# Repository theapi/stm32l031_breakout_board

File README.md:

# STM32L031_breakout_board

Breakout board for the STM32L031 https://www.st.com/en/microcontrollers-microprocessors/stm32l031c4.html

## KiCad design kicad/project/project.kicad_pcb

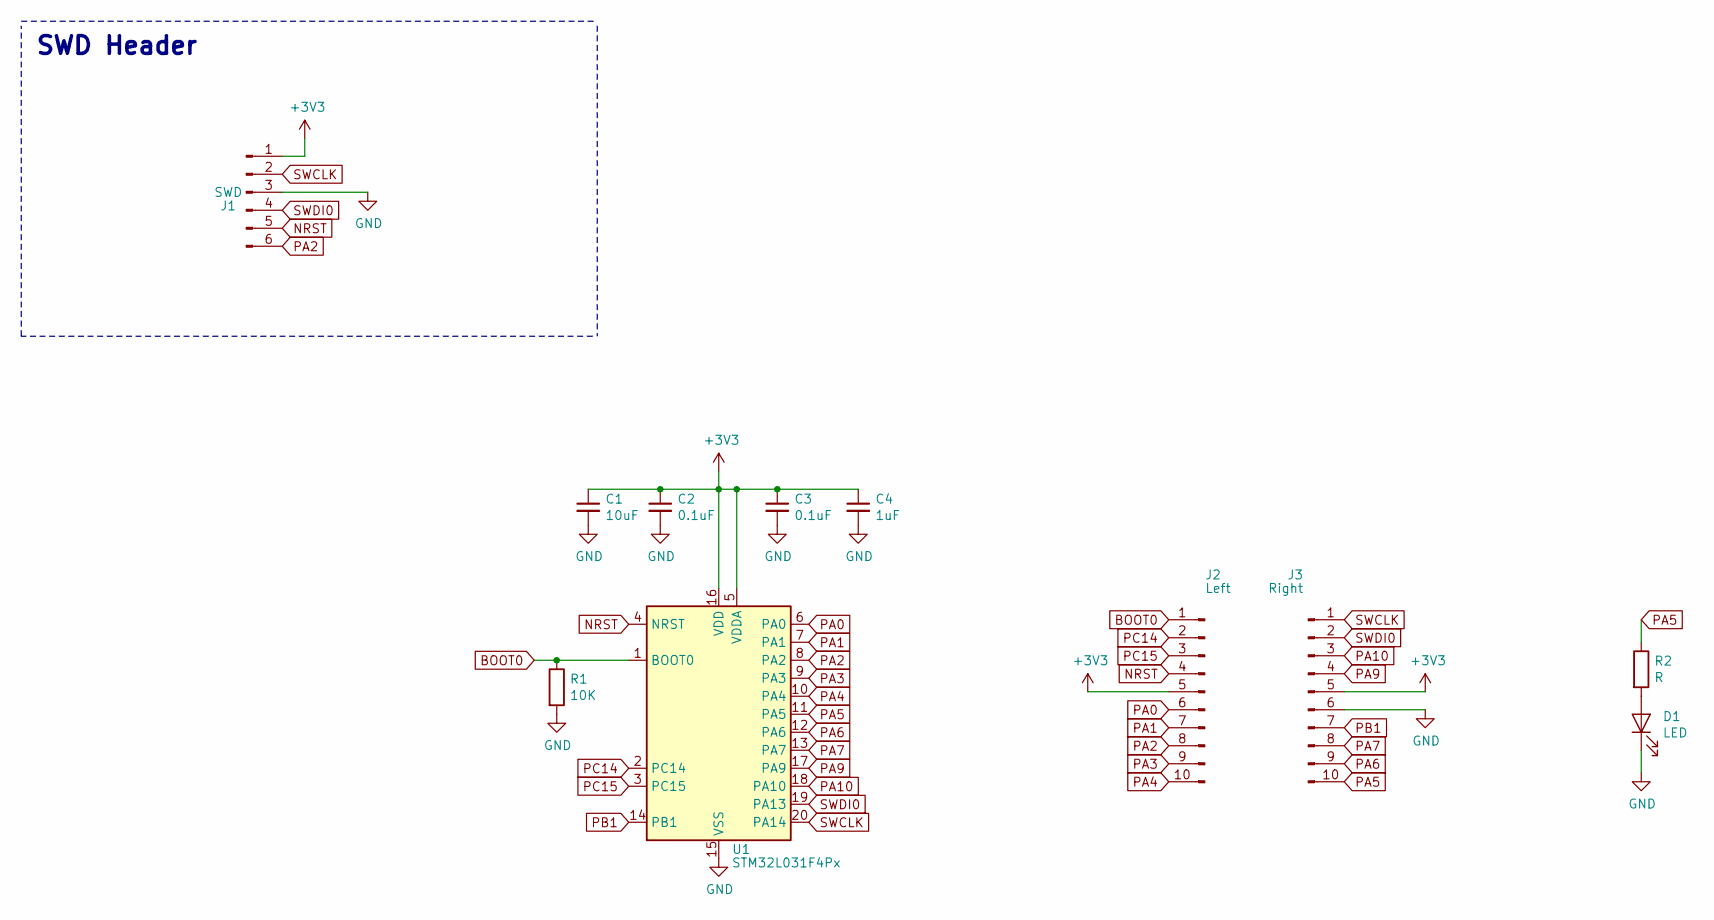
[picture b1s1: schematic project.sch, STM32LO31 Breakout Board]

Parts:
C1: 10uF; C_0603_1608Metric_Pad1.05x0.95mm_HandSolder
C2, C3: 0.1uF; C_0603_1608Metric_Pad1.05x0.95mm_HandSolder
C4: 1uF; C_0603_1608Metric_Pad1.05x0.95mm_HandSolder
D1: LED; LED_0805_2012Metric_Pad1.15x1.40mm_HandSolder
J1: SWD; PinHeader_1x06_P2.54mm_Vertical
J2: Left; PinHeader_1x10_P2.54mm_Vertical
J3: Right; PinHeader_1x10_P2.54mm_Vertical
R1: 10K; R_0603_1608Metric_Pad1.05x0.95mm_HandSolder
R2: R; R_0603_1608Metric_Pad1.05x0.95mm_HandSolder
U1: STM32L031F4Px; TSSOP-20_4.4x6.5mm_P0.65mm

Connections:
+3V3: C1.1, C2.1, C3.1, C4.1, J1.1, J2.5, J3.5, U1.5 (VDDA), U1.16 (VDD)
BOOT0: J2.1, R1.1, U1.1 (BOOT0)
GND: C1.2, C2.2, C3.2, C4.2, D1.1 (K), J1.3, J3.6, R1.2, U1.15 (VSS)
NRST: J1.5, J2.4, U1.4 (NRST)
unnamed: D1.2 (A), R2.2
PA0: J2.6, U1.6 (PA0)
PA1: J2.7, U1.7 (PA1)
PA2: J1.6, J2.8, U1.8 (PA2)
PA3: J2.9, U1.9 (PA3)
PA4: J2.10, U1.10 (PA4)
PA5: J3.10, R2.1, U1.11 (PA5)
PA6: J3.9, U1.12 (PA6)
PA7: J3.8, U1.13 (PA7)
PA9: J3.4, U1.17 (PA9)
PA10: J3.3, U1.18 (PA10)
PB1: J3.7, U1.14 (PB1)
PC14: J2.2, U1.2 (PC14)
PC15: J2.3, U1.3 (PC15)
SWCLK: J1.2, J3.1, U1.20 (PA14)
SWDI0: J1.4, J3.2, U1.19 (PA13)

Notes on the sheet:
SWD Header

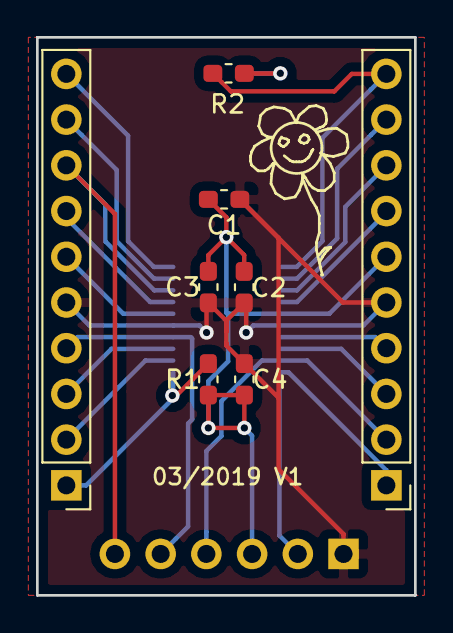
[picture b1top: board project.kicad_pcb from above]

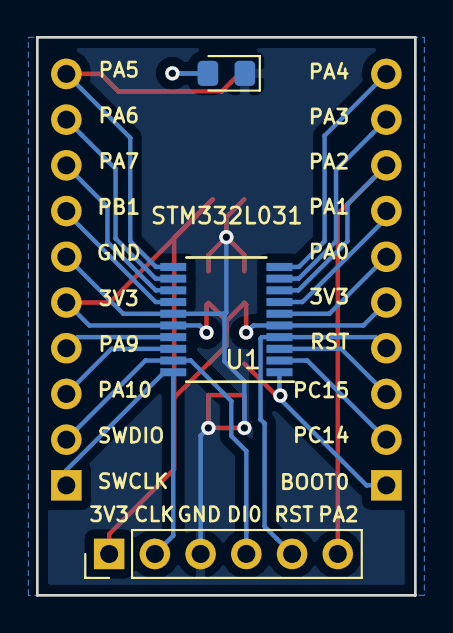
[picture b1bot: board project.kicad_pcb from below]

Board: 2 copper layers, 21.0 x 31.0 mm, 11 parts (3 on the bottom side), 20 nets.

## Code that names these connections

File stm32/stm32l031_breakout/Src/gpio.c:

/**
  ******************************************************************************
  * File Name          : gpio.c
  * Description        : This file provides code for the configuration
  *                      of all used GPIO pins.
  ******************************************************************************
  * @attention
  *
  * <h2><center>&copy; Copyright (c) 2019 STMicroelectronics.
  * All rights reserved.</center></h2>
  *
  * This software component is licensed by ST under BSD 3-Clause license,
  * the "License"; You may not use this file except in compliance with the
  * License. You may obtain a copy of the License at:
  *                        opensource.org/licenses/BSD-3-Clause
  *
  ******************************************************************************
  */

/* Includes ------------------------------------------------------------------*/
#include "gpio.h"
/* USER CODE BEGIN 0 */

/* USER CODE END 0 */

/*----------------------------------------------------------------------------*/
/* Configure GPIO                                                             */
/*----------------------------------------------------------------------------*/
/* USER CODE BEGIN 1 */

/* USER CODE END 1 */

/** Configure pins as 
        * Analog 
        * Input 
        * Output
        * EVENT_OUT
        * EXTI
        * Free pins are configured automatically as Analog (this feature is enabled through 
        * the Code Generation settings)
*/
void MX_GPIO_Init(void)
{

  GPIO_InitTypeDef GPIO_InitStruct = {0};

  /* GPIO Ports Clock Enable */
  __HAL_RCC_GPIOC_CLK_ENABLE();
  __HAL_RCC_GPIOA_CLK_ENABLE();
  __HAL_RCC_GPIOB_CLK_ENABLE();

  /*Configure GPIO pin Output Level */
  HAL_GPIO_WritePin(GPIOC, GPIO_PIN_14|GPIO_PIN_15, GPIO_PIN_RESET);

  /*Configure GPIO pin Output Level */
  HAL_GPIO_WritePin(GPIOA, GPIO_PIN_4|GPIO_PIN_5, GPIO_PIN_RESET);

  /*Configure GPIO pins : PC14 PC15 */
  GPIO_InitStruct.Pin = GPIO_PIN_14|GPIO_PIN_15;
  GPIO_InitStruct.Mode = GPIO_MODE_OUTPUT_PP;
  GPIO_InitStruct.Pull = GPIO_NOPULL;
  GPIO_InitStruct.Speed = GPIO_SPEED_FREQ_LOW;
  HAL_GPIO_Init(GPIOC, &GPIO_InitStruct);

  /*Configure GPIO pins : PA0 PA1 PA6 PA7 
                           PA9 PA10 */
  GPIO_InitStruct.Pin = GPIO_PIN_0|GPIO_PIN_1|GPIO_PIN_6|GPIO_PIN_7 
                          |GPIO_PIN_9|GPIO_PIN_10;
  GPIO_InitStruct.Mode = GPIO_MODE_ANALOG;
  GPIO_InitStruct.Pull = GPIO_NOPULL;
  HAL_GPIO_Init(GPIOA, &GPIO_InitStruct);

  /*Configure GPIO pins : PA4 PA5 */
  GPIO_InitStruct.Pin = GPIO_PIN_4|GPIO_PIN_5;
  GPIO_InitStruct.Mode = GPIO_MODE_OUTPUT_PP;
  GPIO_InitStruct.Pull = GPIO_NOPULL;
  GPIO_InitStruct.Speed = GPIO_SPEED_FREQ_LOW;
  HAL_GPIO_Init(GPIOA, &GPIO_InitStruct);

  /*Configure GPIO pin : PB1 */
  GPIO_InitStruct.Pin = GPIO_PIN_1;
  GPIO_InitStruct.Mode = GPIO_MODE_ANALOG;
  GPIO_InitStruct.Pull = GPIO_NOPULL;
  HAL_GPIO_Init(GPIOB, &GPIO_InitStruct);

}

/* USER CODE BEGIN 2 */

/* USER CODE END 2 */

/************************ (C) COPYRIGHT STMicroelectronics *****END OF FILE****/

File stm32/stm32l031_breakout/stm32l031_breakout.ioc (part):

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Mcu.Name=STM32L031F(4-6)Px
Mcu.Package=TSSOP20
Mcu.UserName=STM32L031F4Px
PA13.Mode=Serial_Wire
PA13.Signal=SYS_SWDIO
PA14.Mode=Serial_Wire
PA14.Signal=SYS_SWCLK
PA2.Mode=Asynchronous
PA2.Signal=USART2_TX
PA3.Mode=Asynchronous
PA3.Signal=USART2_RX
PA4.Signal=GPIO_Output
PA5.Signal=GPIO_Output
PC14-OSC32_IN.Signal=GPIO_Output
PC15-OSC32_OUT.Signal=GPIO_Output
RCC.HSE_VALUE=8000000
RCC.SYSCLKFreq_VALUE=2097000
board=custom

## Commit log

2019-03-09 Breakout board
2019-03-12 Labels
2019-03-12 Decoration
2019-03-13 Gerbers
2019-04-02 Blinky
2019-04-04 More outputs high
